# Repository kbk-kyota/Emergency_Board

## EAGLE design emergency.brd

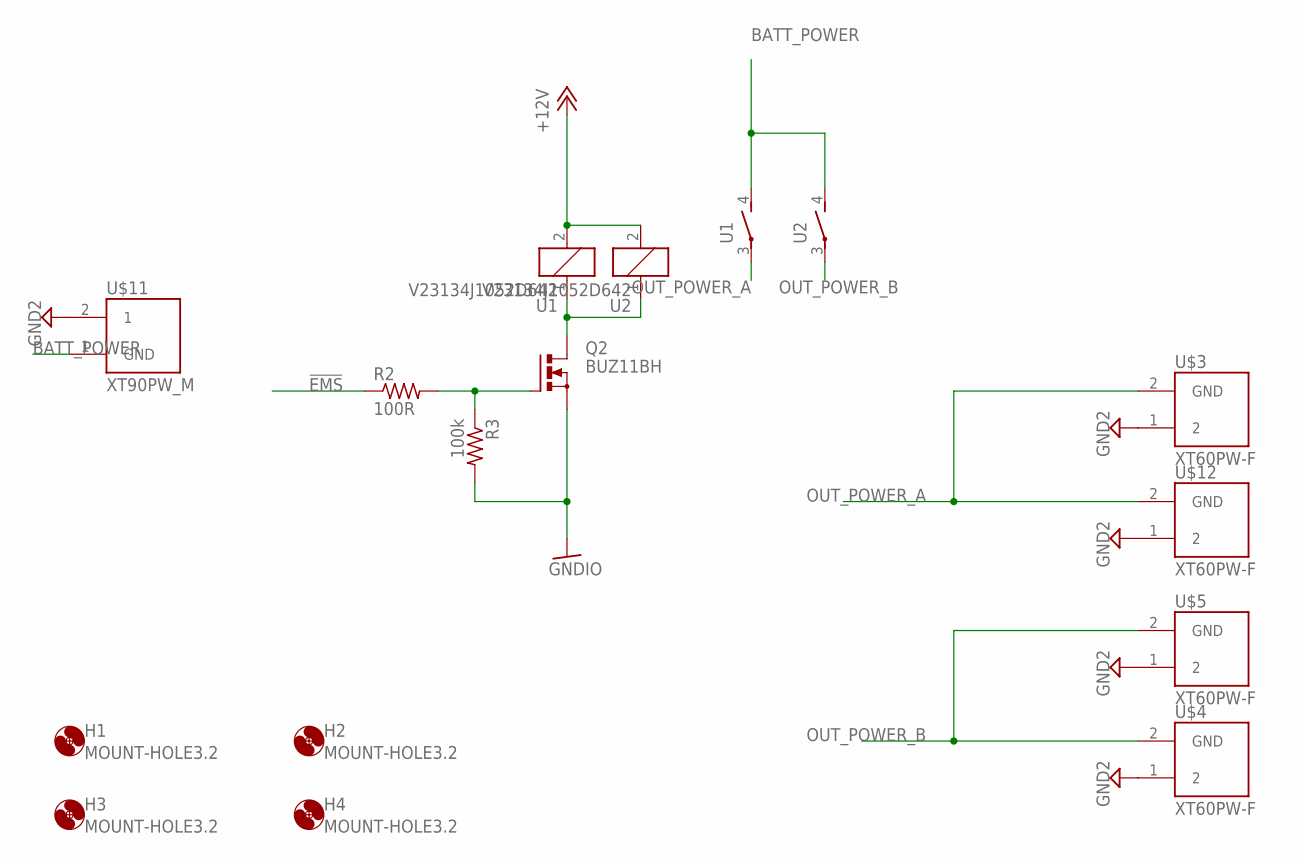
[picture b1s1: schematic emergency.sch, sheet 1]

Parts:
H1, H2, H3, H4: MOUNT-HOLE3.2; 3,2
Q2: BUZ11BH; TO220BH
R2: 100R; R0603
R3: 100k; R0603
U1, U2: V23134J1052D642
U$3, U$4, U$5, U$12: XT60PW-F; AMASS_XT60PW-F
U$11: XT90PW_M; AMASS_XT90PW_M

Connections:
!EMS: R2.1; also elsewhere on the board
+12V: U1.2, U2.2; also elsewhere on the board
BATT_POWER: U1.4 (S), U2.4 (S), U$11.1 (GND)
GND2: U$3.1 (2), U$4.1 (2), U$5.1 (2), U$11.2 (1), U$12.1 (2)
GNDIO: Q2.S, R3.2; also elsewhere on the board
unnamed: Q2.D, U1.1, U2.1
unnamed: Q2.G, R2.2, R3.1
OUT_POWER_A: U1.3, U$3.2 (GND), U$12.2 (GND)
OUT_POWER_B: U2.3, U$4.2 (GND), U$5.2 (GND)

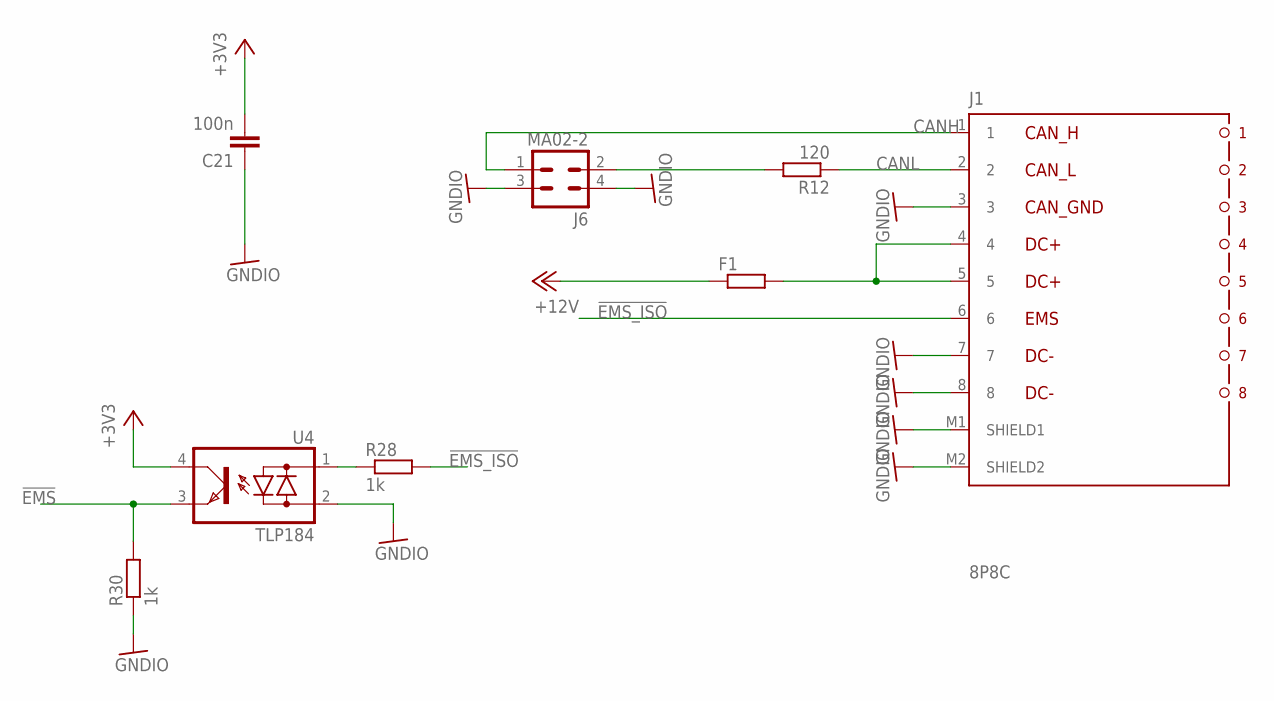
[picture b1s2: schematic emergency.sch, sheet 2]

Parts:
C21: 100n; C0603
F1: R-EU_R1206; R1206
J1: 8P8C
J6: MA02-2; MA02-2W
R12: 120; R0603
R28, R30: 1k; R0603
U4: TLP184; 11-4M1S

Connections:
!EMS: R30.2, U4.3 (E); also elsewhere on the board
!EMS_ISO: J1.6, R28.2
+3V3: C21.2, U4.4 (C); also elsewhere on the board
+12V: F1.1; also elsewhere on the board
CANH: J1.1, J6.1
CANL: J1.2, R12.1
GNDIO: C21.1, J1.3, J1.7, J1.8, J1.M1 (SHIELD1), J1.M2 (SHIELD2), J6.3, J6.4, R30.1, U4.2 (AC2); also elsewhere on the board
unnamed: F1.2, J1.4, J1.5
unnamed: J6.2, R12.2
unnamed: R28.1, U4.1 (AC1)

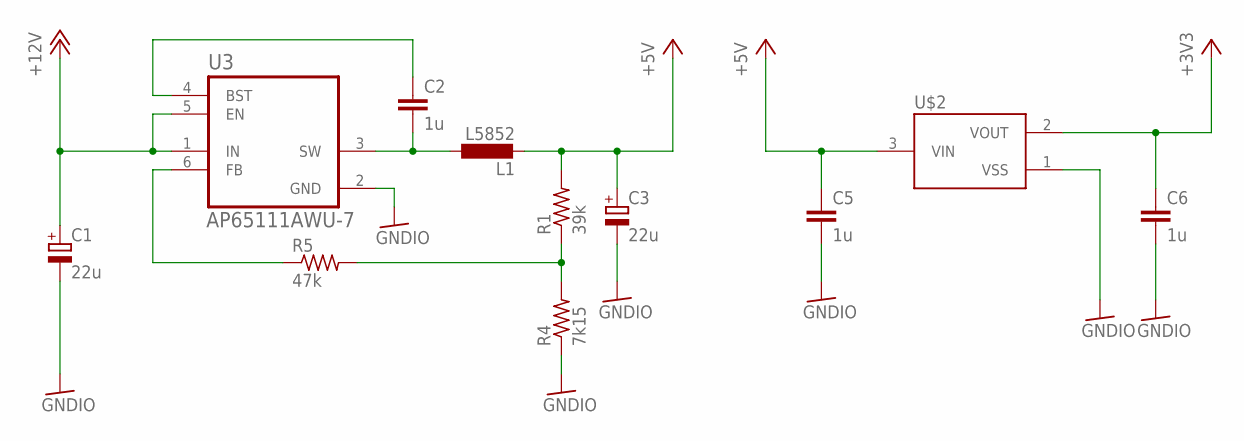
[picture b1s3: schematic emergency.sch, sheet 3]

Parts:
C1, C3: 22u; E2-5
C2, C5, C6: 1u; C0603
L1: L5852
R1: 39k; R0603
R4: 7k15; R0603
R5: 47k; R0603
U3: AP65111AWU-7; SOT95P280X100-6N
U$2: AP2120; SOT95P240X110-3

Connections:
+3V3: C6.1, U$2.2 (VOUT); also elsewhere on the board
+5V: C3.+, C5.1, L1.P$2 (2), R1.2, U$2.3 (VIN)
+12V: C1.+, U3.1 (IN), U3.5 (EN); also elsewhere on the board
GNDIO: C1.-, C3.-, C5.2, C6.2, R4.1, U3.2 (GND), U$2.1 (VSS); also elsewhere on the board
unnamed: C2.2, L1.P$1 (1), U3.3 (SW)
unnamed: C2.1, U3.4 (BST)
unnamed: R1.1, R4.2, R5.2
unnamed: R5.1, U3.6 (FB)

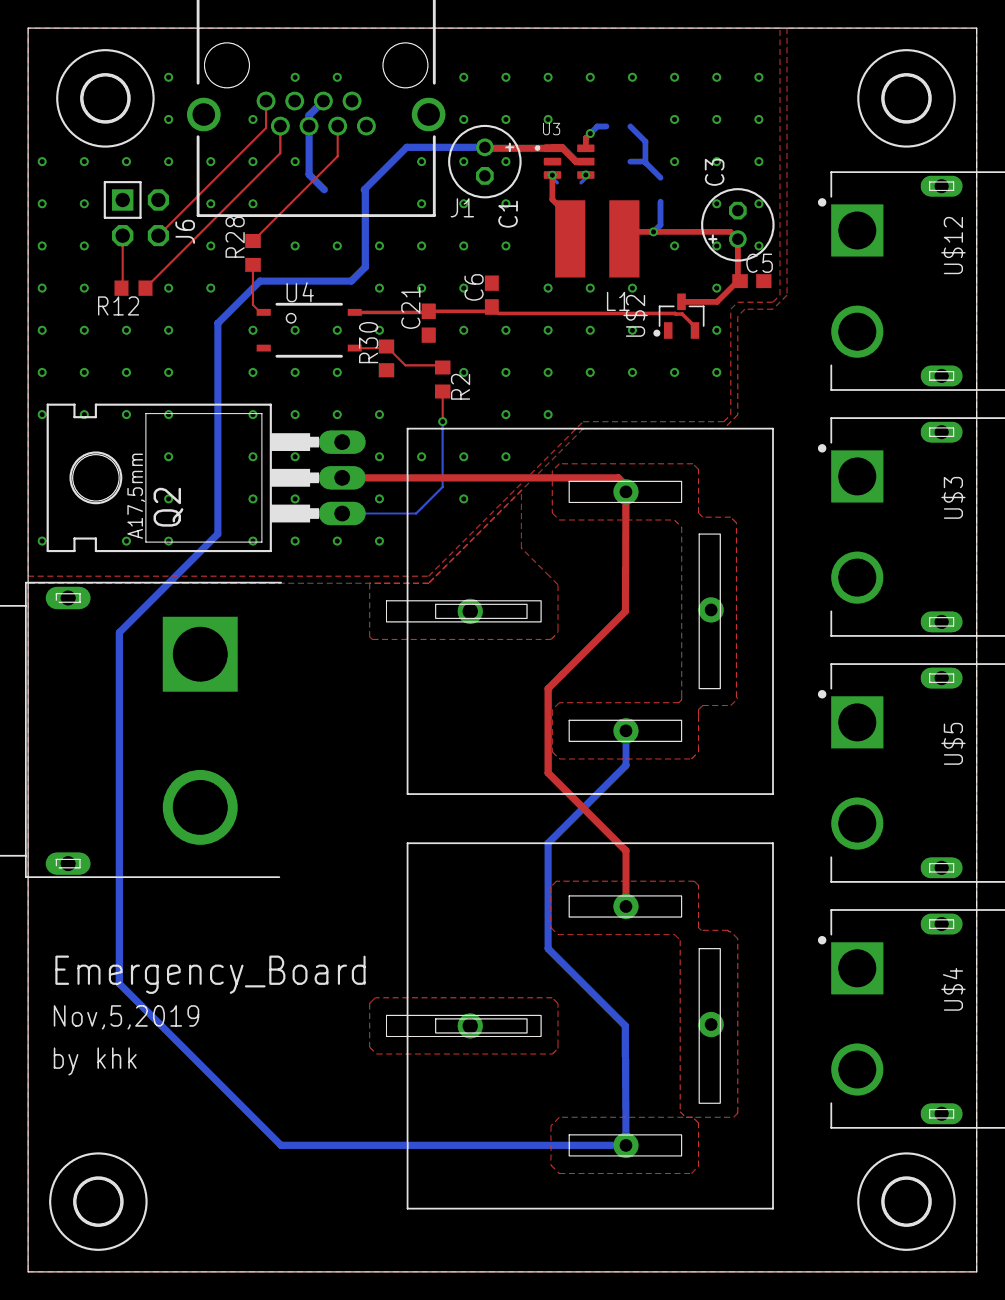
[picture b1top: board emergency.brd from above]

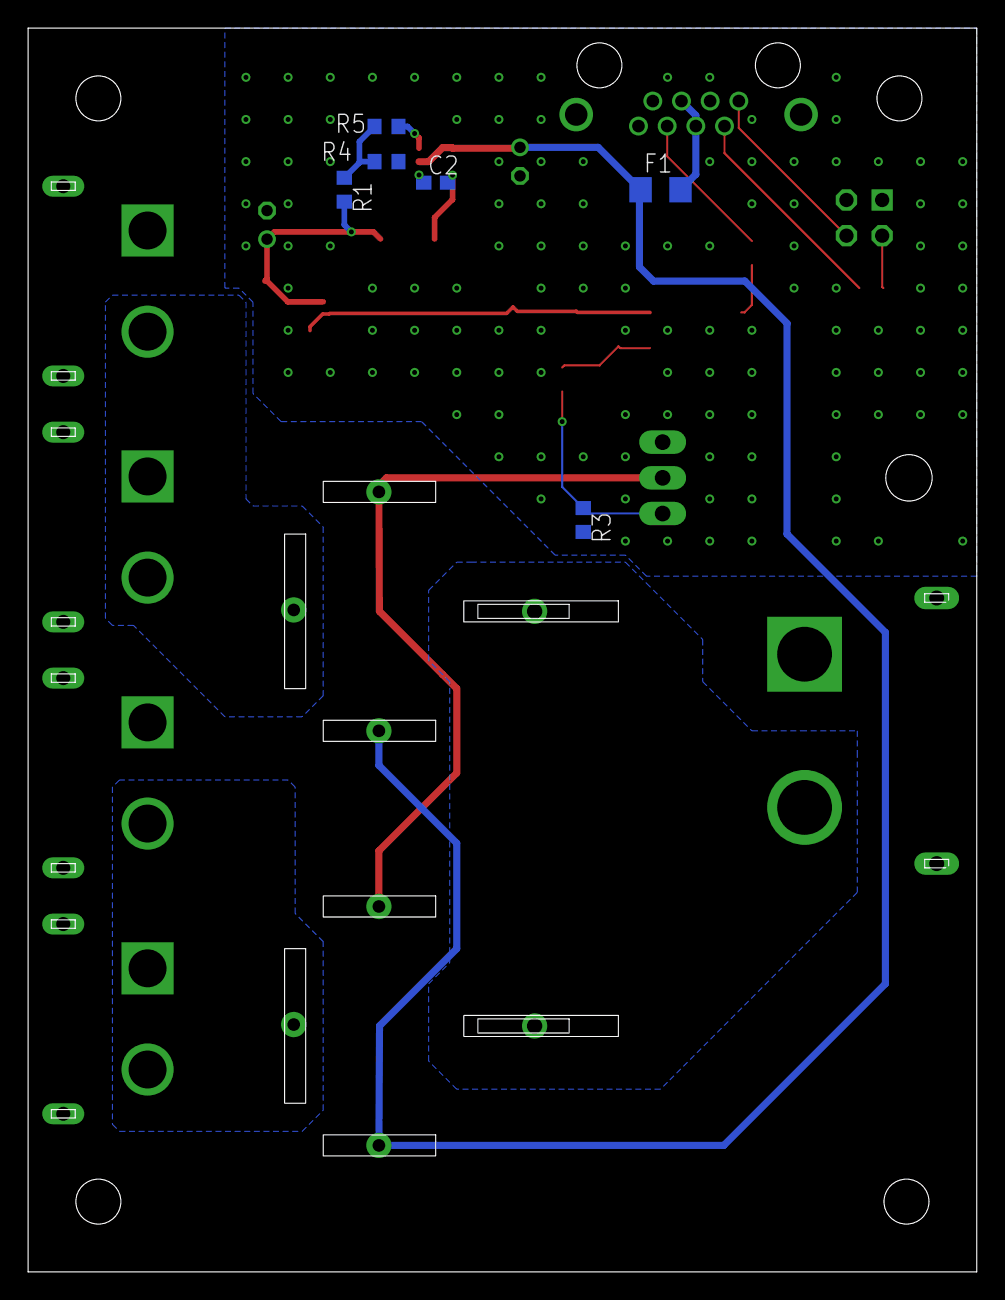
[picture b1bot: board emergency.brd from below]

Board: 2 copper layers, 67.5 x 88.5 mm, 33 parts (6 on the bottom side), 21 nets.

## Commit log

2019-09-07 prototype
2019-09-08 GNDIOのベタにビアを打った
2019-09-08 コイルの配線とベタの修正
2019-11-06 リレーのライブラリの修正
